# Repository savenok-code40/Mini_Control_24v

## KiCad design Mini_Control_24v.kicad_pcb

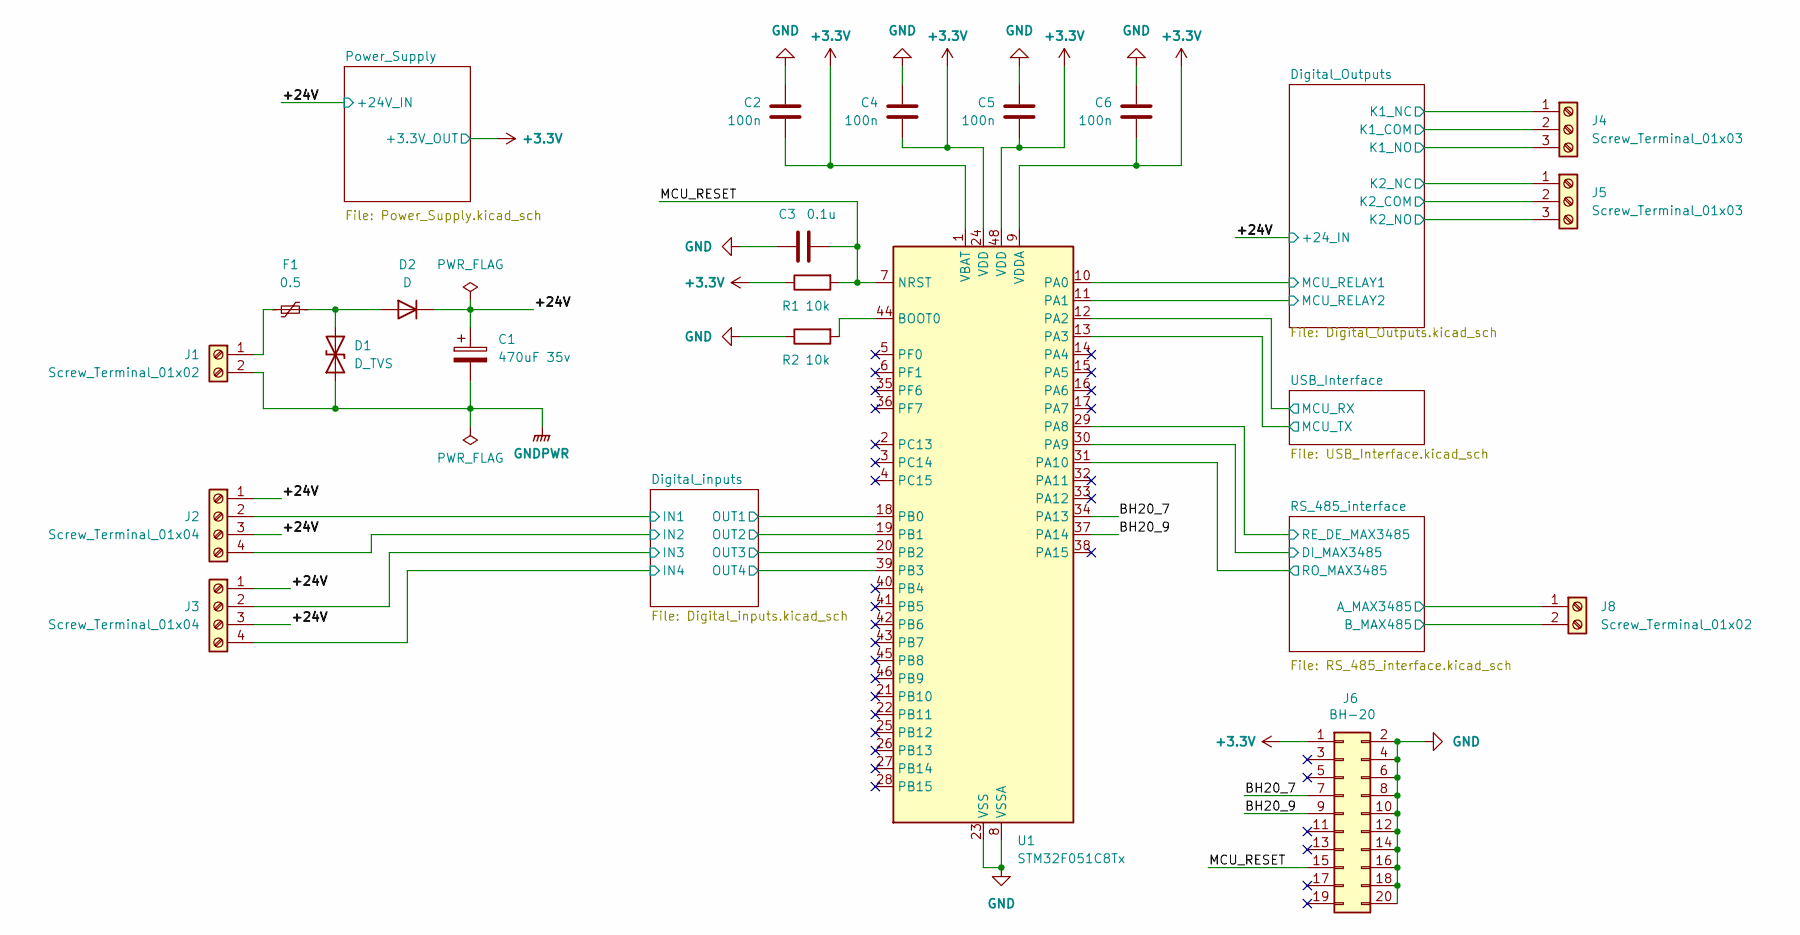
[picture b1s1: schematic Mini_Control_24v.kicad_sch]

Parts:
C1: 470uF 35v; CP_Elec_10x10.5
C2, C4, C5, C6: 100n; C_1206_3216Metric; MPN CC1206KKX7R9BB104
C3: 0.1u; C_1206_3216Metric
D1: D_TVS; D_SMB; MPN SMBJ30A
D2: D; D_SMC
F1: 0.5; Fuse_1812_4532Metric; MPN MF-MSMF050/30X-2
J1: Screw_Terminal_01x02; PhoenixContact_MSTBA_2,5_2-G-5,08_1x02_P5.08mm_Horizontal; MPN 1757242
J2, J3: Screw_Terminal_01x04; PhoenixContact_MSTBA_2,5_4-G-5,08_1x04_P5.08mm_Horizontal; MPN 1757268
J4, J5: Screw_Terminal_01x03; PhoenixContact_MSTBA_2,5_3-G-5,08_1x03_P5.08mm_Horizontal
J6: ВН-20; IDC-Header_2x10_P2.54mm_Vertical_SMD; MPN BH-20
J8: Screw_Terminal_01x02; PhoenixContact_MSTBA_2,5_2-G-5,08_1x02_P5.08mm_Horizontal
R1, R2: 10k; R_1206_3216Metric; MPN RC1206FR-0710KL
U1: STM32F051C8Tx; LQFP-48_7x7mm_P0.5mm; MPN STM32F051C8T6

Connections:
+3.3V: C2.1, C4.1, C5.1, C6.1, J6.1, R1.1, U1.1 (VBAT), U1.9 (VDDA), U1.24 (VDD), U1.48 (VDD); also elsewhere on the board
/+24V: C1.1, D2.1 (K), J2.1, J2.3, J3.1, J3.3; also elsewhere on the board
/Digital_Outputs/K1_COM: J4.2; also elsewhere on the board
/Digital_Outputs/K1_NC: J4.1; also elsewhere on the board
/Digital_Outputs/K1_NO: J4.3; also elsewhere on the board
/Digital_Outputs/K2_COM: J5.2; also elsewhere on the board
/Digital_Outputs/K2_NC: J5.1; also elsewhere on the board
/Digital_Outputs/K2_NO: J5.3; also elsewhere on the board
/Digital_Outputs/MCU_RELAY1: U1.10 (PA0); also elsewhere on the board
/Digital_Outputs/MCU_RELAY2: U1.11 (PA1); also elsewhere on the board
/Digital_inputs/IN1: J2.2; also elsewhere on the board
/Digital_inputs/IN2: J2.4; also elsewhere on the board
/Digital_inputs/IN3: J3.2; also elsewhere on the board
/Digital_inputs/IN4: J3.4; also elsewhere on the board
/Digital_inputs/OUT1: U1.18 (PB0); also elsewhere on the board
/Digital_inputs/OUT2: U1.19 (PB1); also elsewhere on the board
/Digital_inputs/OUT3: U1.20 (PB2); also elsewhere on the board
/Digital_inputs/OUT4: U1.39 (PB3); also elsewhere on the board
/MCU_RESET: C3.2, J6.15, R1.2, U1.7 (NRST)
/RS_485_interface/A_MAX3485: J8.1; also elsewhere on the board
/RS_485_interface/B_MAX485: J8.2; also elsewhere on the board
/RS_485_interface/DI_MAX3485: U1.30 (PA9); also elsewhere on the board
/RS_485_interface/RE_DE_MAX3485: U1.29 (PA8); also elsewhere on the board
/RS_485_interface/RO_MAX3485: U1.31 (PA10); also elsewhere on the board
/USB_Interface/MCU_RX: U1.12 (PA2); also elsewhere on the board
/USB_Interface/MCU_TX: U1.13 (PA3); also elsewhere on the board
/ВН20_7: J6.7, U1.34 (PA13)
/ВН20_9: J6.9, U1.37 (PA14)
GND: C2.2, C3.1, C4.2, C5.2, C6.2, J6.2, J6.4, J6.6, J6.8, J6.10, J6.12, J6.14, J6.16, J6.18, J6.20, R2.1, U1.8 (VSSA), U1.23 (VSS), U1.47 (VSS); also elsewhere on the board
GNDPWR: C1.2, D1.1 (A1), J1.2; also elsewhere on the board
unnamed: D1.2 (A2), D2.2 (A), F1.2
unnamed: F1.1, J1.1
unnamed: R2.2, U1.44 (BOOT0)

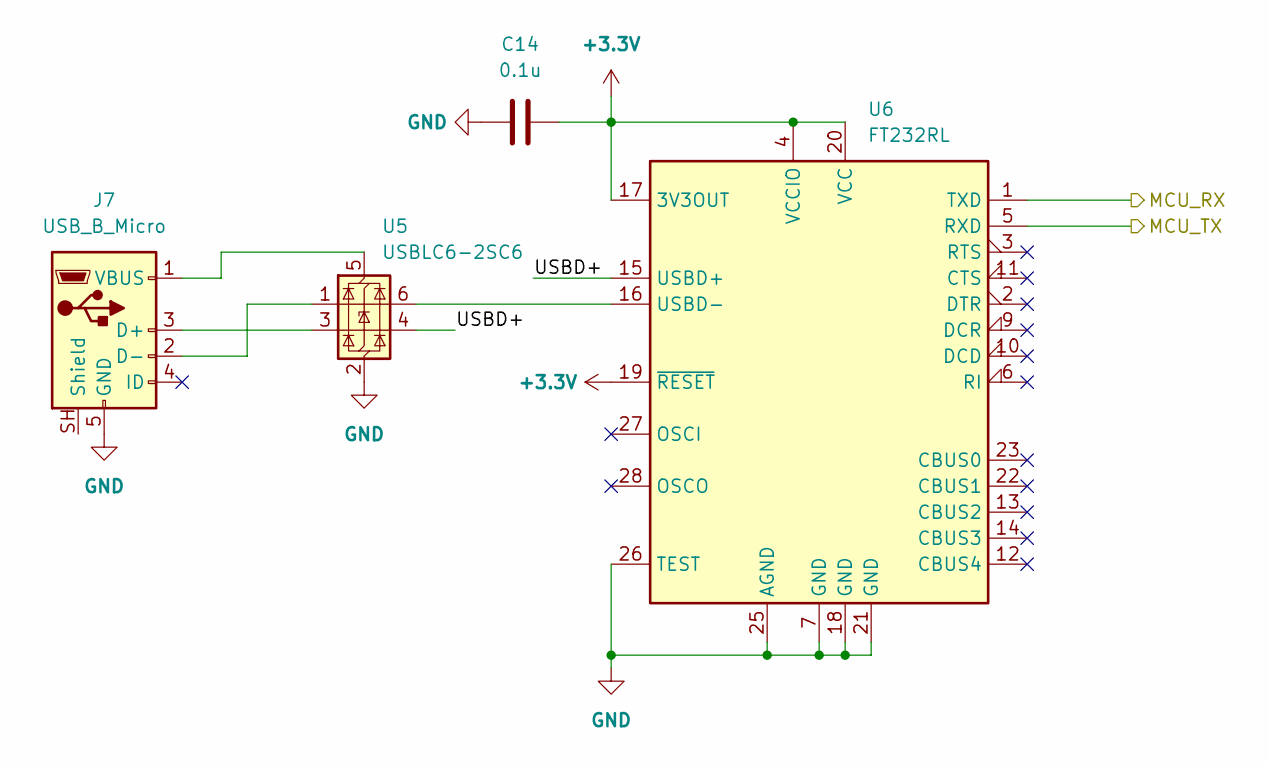
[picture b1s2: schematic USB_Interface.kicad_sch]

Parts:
C14: 0.1u; C_1206_3216Metric
J7: USB_B_Micro; USB_Micro-B_Molex-105017-0001; MPN 105017-0001
U5: USBLC6-2SC6; SOT-23-6; MPN USBLC6-2SC6
U6: FT232RL; SSOP-28_5.3x10.2mm_P0.65mm; MPN FT232RL-REEL

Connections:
+3.3V: C14.2, U6.4 (VCCIO), U6.17 (3V3OUT), U6.19 (~RESET), U6.20 (VCC); also elsewhere on the board
/USB_Interface/MCU_RX: U6.1 (TXD); also elsewhere on the board
/USB_Interface/MCU_TX: U6.5 (RXD); also elsewhere on the board
/USB_Interface/USBD+: U5.4 (I/O2), U6.15 (USBD+)
GND: C14.1, J7.5 (GND), U5.2 (GND), U6.7 (GND), U6.18 (GND), U6.21 (GND), U6.25 (AGND), U6.26 (TEST); also elsewhere on the board
unnamed: J7.3 (D+), U5.3 (I/O2)
unnamed: J7.2 (D-), U5.1 (I/O1)
unnamed: J7.1 (VBUS), U5.5 (VBUS)
unnamed: U5.6 (I/O1), U6.16 (USBD-)

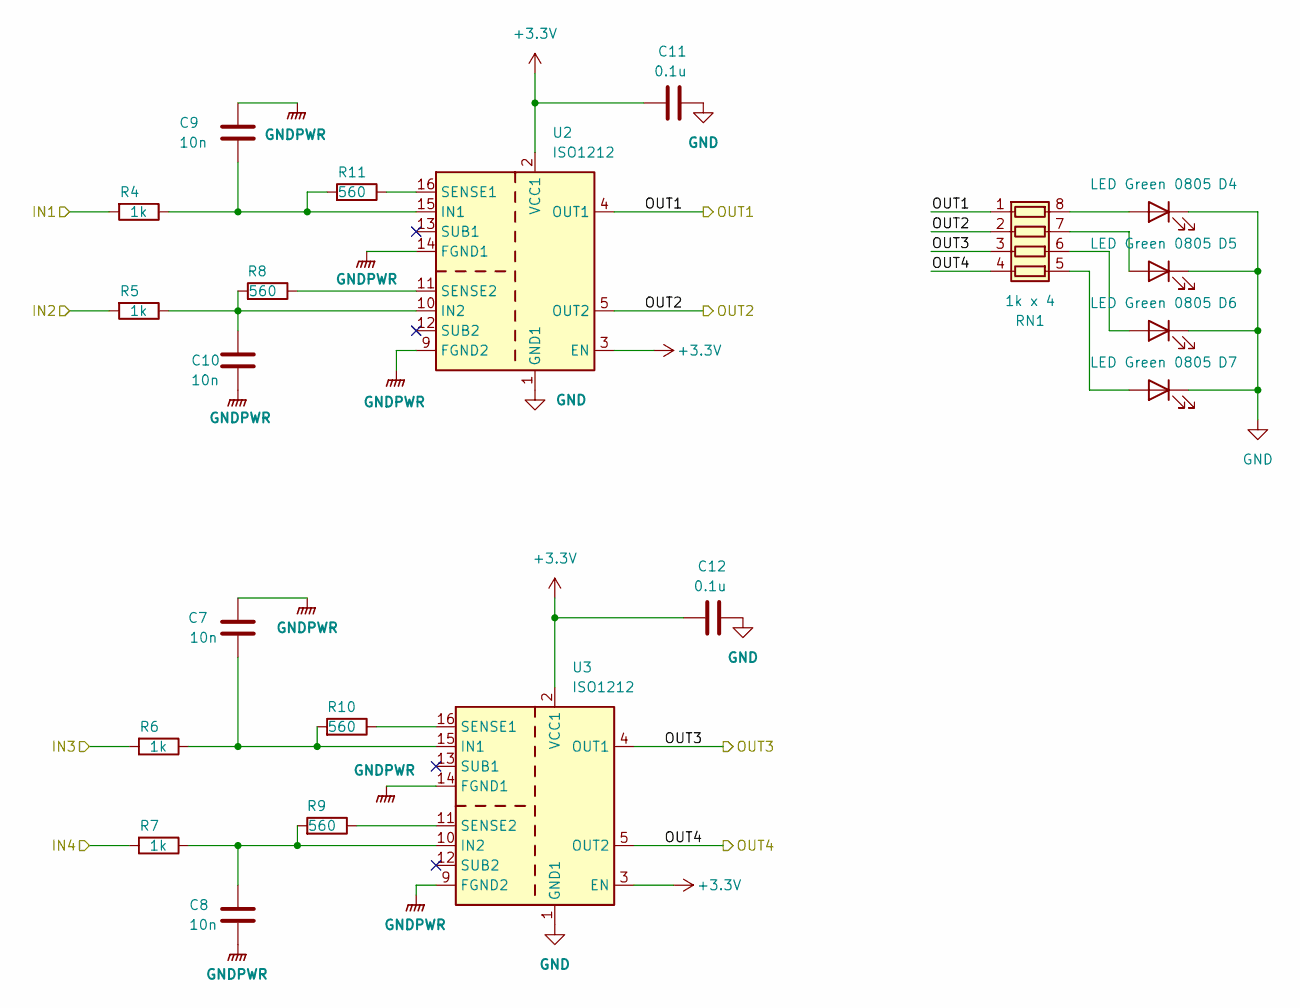
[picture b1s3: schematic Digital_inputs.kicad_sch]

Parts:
C7, C8, C9, C10: 10n; C_1206_3216Metric; MPN CC1206KKX7R9BB103
C11, C12: 0.1u; C_1206_3216Metric
D4, D5, D6, D7: LED Green 0805; LED_1206_3216Metric; MPN FYLS-1206PGC
R4, R5, R6, R7: 1k; R_1206_3216Metric; MPN RC1206FR-071KL
R8, R9, R10, R11: 560; R_1206_3216Metric; MPN RC1206FR-07560RL
RN1: 1k x 4; R_Array_Concave_4x0603; MPN CAT16-102J4
U2, U3: ISO1212; SSOP-16_3.9x4.9mm_P0.635mm; MPN ISO1212DBQ

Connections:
+3.3V: C11.1, C12.1, U2.2 (VCC1), U2.3 (EN), U3.2 (VCC1), U3.3 (EN); also elsewhere on the board
/Digital_inputs/IN1: R4.2; also elsewhere on the board
/Digital_inputs/IN2: R5.2; also elsewhere on the board
/Digital_inputs/IN3: R6.2; also elsewhere on the board
/Digital_inputs/IN4: R7.2; also elsewhere on the board
/Digital_inputs/OUT1: RN1.1 (R1.1), U2.4 (OUT1); also elsewhere on the board
/Digital_inputs/OUT2: RN1.2 (R2.1), U2.5 (OUT2); also elsewhere on the board
/Digital_inputs/OUT3: RN1.3 (R3.1), U3.4 (OUT1); also elsewhere on the board
/Digital_inputs/OUT4: RN1.4 (R4.1), U3.5 (OUT2); also elsewhere on the board
GND: C11.2, C12.2, D4.1 (K), D5.1 (K), D6.1 (K), D7.1 (K), U2.1 (GND1), U2.8 (GND1), U3.1 (GND1), U3.8 (GND1); also elsewhere on the board
GNDPWR: C7.1, C8.1, C9.2, C10.2, U2.9 (FGND2), U2.14 (FGND1), U3.9 (FGND2), U3.14 (FGND1); also elsewhere on the board
unnamed: D4.2 (A), RN1.8 (R1.2)
unnamed: D5.2 (A), RN1.7 (R2.2)
unnamed: D6.2 (A), RN1.6 (R3.2)
unnamed: D7.2 (A), RN1.5 (R4.2)
unnamed: C9.1, R4.1, R11.2, U2.15 (IN1)
unnamed: C10.1, R5.1, R8.2, U2.10 (IN2)
unnamed: R11.1, U2.16 (SENSE1)
unnamed: R8.1, U2.11 (SENSE2)
unnamed: C7.2, R6.1, R10.2, U3.15 (IN1)
unnamed: C8.2, R7.1, R9.2, U3.10 (IN2)
unnamed: R10.1, U3.16 (SENSE1)
unnamed: R9.1, U3.11 (SENSE2)

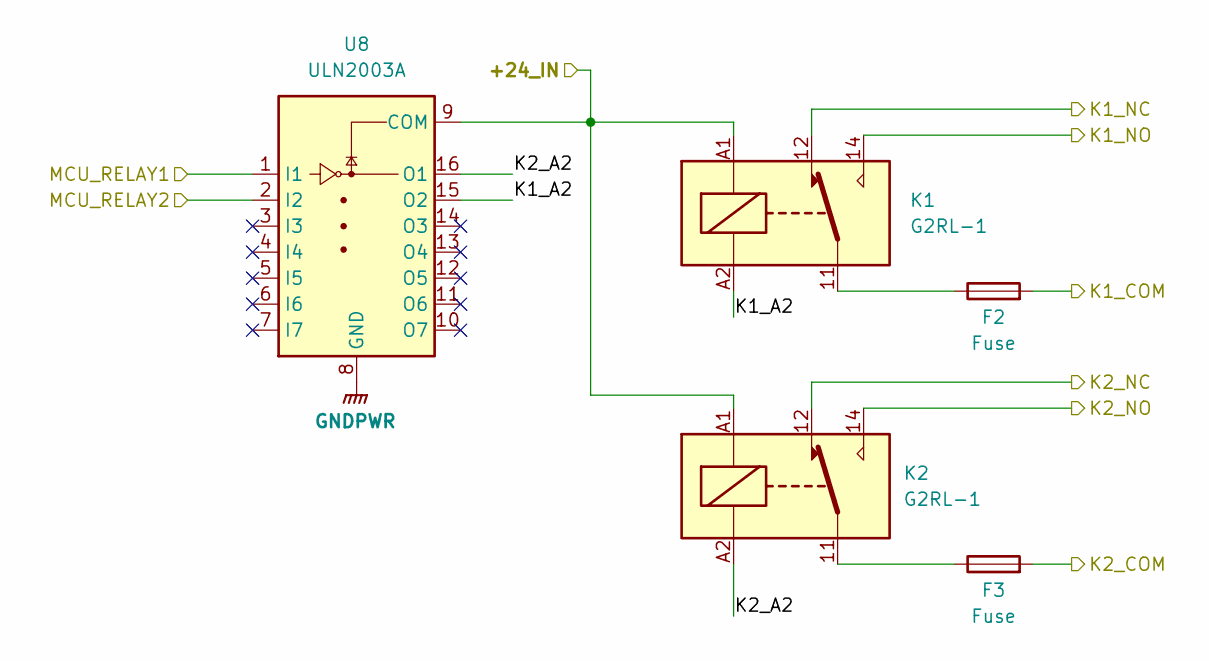
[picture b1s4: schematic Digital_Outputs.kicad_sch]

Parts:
F2, F3: Fuse; Fuse_2512_6332Metric_Pad1.52x3.35mm_HandSolder
K1, K2: G2RL-1; Relay_SPDT_Omron_G2RL-1; MPN G2RL-1 24DC
U8: ULN2003A; SOIC-16_3.9x9.9mm_P1.27mm; MPN ULN2003ADR

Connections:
/+24V: K1.A1, K2.A1, U8.9 (COM); also elsewhere on the board
/Digital_Outputs/K1_A2: K1.A2, U8.15 (O2)
/Digital_Outputs/K1_COM: F2.2; also elsewhere on the board
/Digital_Outputs/K1_NC: K1.12; also elsewhere on the board
/Digital_Outputs/K1_NO: K1.14; also elsewhere on the board
/Digital_Outputs/K2_A2: K2.A2, U8.16 (O1)
/Digital_Outputs/K2_COM: F3.2; also elsewhere on the board
/Digital_Outputs/K2_NC: K2.12; also elsewhere on the board
/Digital_Outputs/K2_NO: K2.14; also elsewhere on the board
/Digital_Outputs/MCU_RELAY1: U8.1 (I1); also elsewhere on the board
/Digital_Outputs/MCU_RELAY2: U8.2 (I2); also elsewhere on the board
GNDPWR: U8.8 (GND); also elsewhere on the board
unnamed: F2.1, K1.11
unnamed: F3.1, K2.11

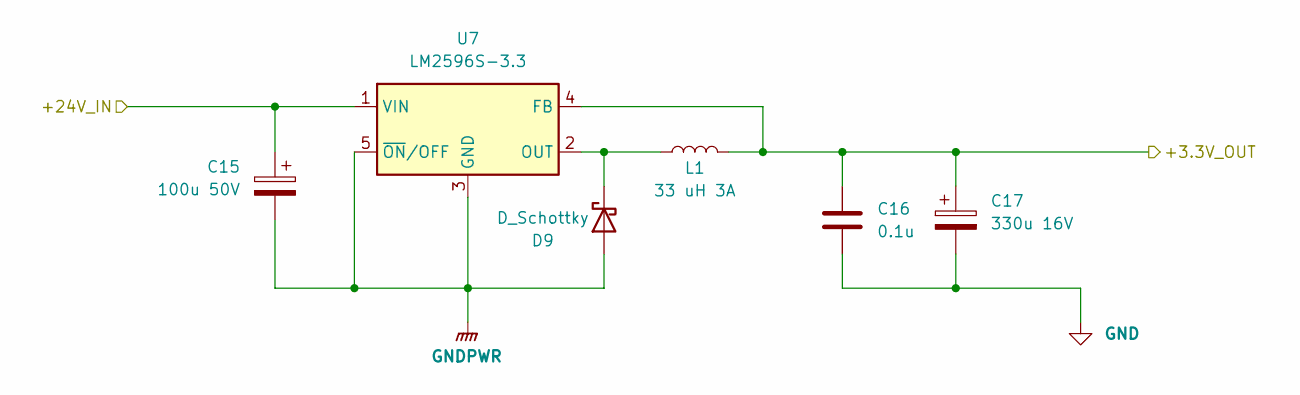
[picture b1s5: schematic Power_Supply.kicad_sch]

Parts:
C15: 100u 50V; CP_Elec_10x10.5
C16: 0.1u; C_1206_3216Metric
C17: 330u 16V; CP_Elec_8x10.5
D9: D_Schottky; TO-263-2_TabPin1; MPN MBRD1045T4G
L1: 33 uH 3A; L_10.4x10.4_H4.8; MPN SDR1006-330KL
U7: LM2596S-3.3; TO-263-5_TabPin3; MPN LM2596S-3.3

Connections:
+3.3V: C16.1, C17.1, L1.2, U7.4 (FB); also elsewhere on the board
/+24V: C15.1, U7.1 (VIN); also elsewhere on the board
GND: C16.2, C17.2; also elsewhere on the board
GNDPWR: C15.2, D9.2 (A), U7.3 (GND), U7.5 (~ON/OFF); also elsewhere on the board
unnamed: D9.1 (K), L1.1, U7.2 (OUT)

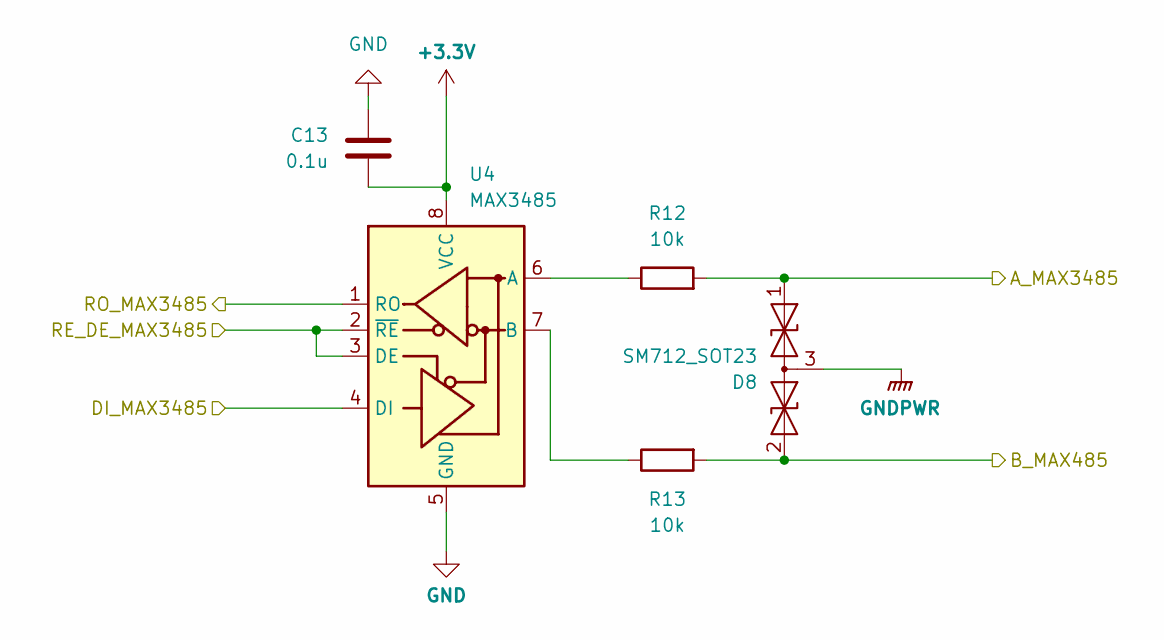
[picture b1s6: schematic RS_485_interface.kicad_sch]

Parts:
C13: 0.1u; C_1206_3216Metric
D8: SM712_SOT23; SOT-23; MPN SM712-02HTG
R12, R13: 10k; R_1206_3216Metric; MPN RC1206FR-0710KL
U4: MAX3485; SOIC-8_3.9x4.9mm_P1.27mm; MPN MAX3485EESA+T

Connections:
+3.3V: C13.2, U4.8 (VCC); also elsewhere on the board
/RS_485_interface/A_MAX3485: D8.1 (A1), R12.2; also elsewhere on the board
/RS_485_interface/B_MAX485: D8.2 (A2), R13.2; also elsewhere on the board
/RS_485_interface/DI_MAX3485: U4.4 (DI); also elsewhere on the board
/RS_485_interface/RE_DE_MAX3485: U4.2 (~RE), U4.3 (DE); also elsewhere on the board
/RS_485_interface/RO_MAX3485: U4.1 (RO); also elsewhere on the board
GND: C13.1, U4.5 (GND); also elsewhere on the board
GNDPWR: D8.3 (common); also elsewhere on the board
unnamed: R12.1, U4.6 (A)
unnamed: R13.1, U4.7 (B)

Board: 2 copper layers, 60 parts (0 on the bottom side), 57 nets, no tracks yet.
